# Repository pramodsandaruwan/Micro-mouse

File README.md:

# Micro-mouse
Maze solving micro-mouse robot by Pramod sandaruwan

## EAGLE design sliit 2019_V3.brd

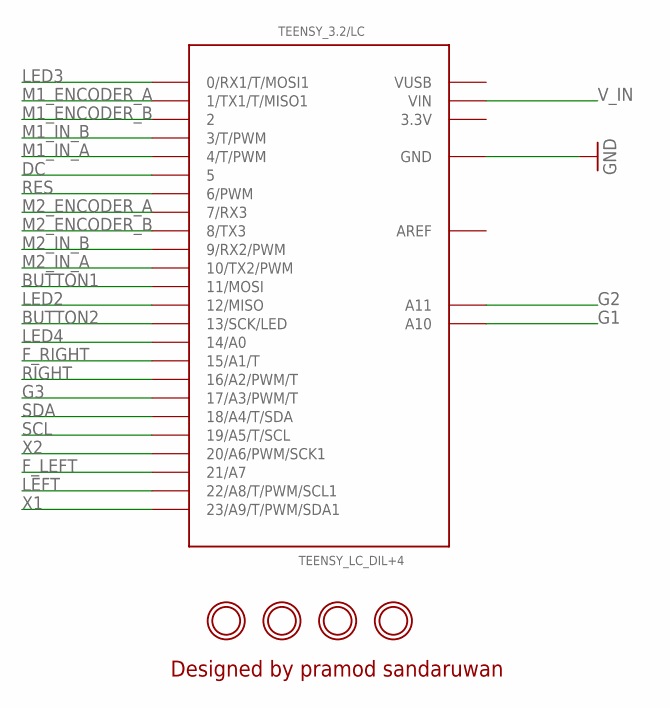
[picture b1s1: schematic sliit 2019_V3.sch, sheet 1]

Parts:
TEENSY_3.2/LC: TEENSY_LC_DIL+4; TEENSY3-DIL+4
U$7, U$10, U$11, U$12: MOUNTINGHOLE2.5; MOUNTINGHOLE_2.5_PLATED

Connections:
3.3V: TEENSY_3.2/LC.3.3V
AREF: TEENSY_3.2/LC.AREF
BUTTON1: TEENSY_3.2/LC.11 (11/MOSI); also elsewhere on the board
BUTTON2: TEENSY_3.2/LC.13 (13/SCK/LED); also elsewhere on the board
DC: TEENSY_3.2/LC.5; also elsewhere on the board
F_LEFT: TEENSY_3.2/LC.21/A7; also elsewhere on the board
F_RIGHT: TEENSY_3.2/LC.15/A1 (15/A1/T); also elsewhere on the board
G1: TEENSY_3.2/LC.A10; also elsewhere on the board
G2: TEENSY_3.2/LC.A11; also elsewhere on the board
G3: TEENSY_3.2/LC.17/A3 (17/A3/PWM/T); also elsewhere on the board
GND: TEENSY_3.2/LC.AGND (GND), TEENSY_3.2/LC.GND; also elsewhere on the board
LED2: TEENSY_3.2/LC.12 (12/MISO); also elsewhere on the board
LED3: TEENSY_3.2/LC.0 (0/RX1/T/MOSI1); also elsewhere on the board
LED4: TEENSY_3.2/LC.14/A0; also elsewhere on the board
LEFT: TEENSY_3.2/LC.22/A8 (22/A8/T/PWM/SCL1); also elsewhere on the board
M1_ENCODER_A: TEENSY_3.2/LC.1 (1/TX1/T/MISO1); also elsewhere on the board
M1_ENCODER_B: TEENSY_3.2/LC.2; also elsewhere on the board
M1_IN_A: TEENSY_3.2/LC.4 (4/T/PWM); also elsewhere on the board
M1_IN_B: TEENSY_3.2/LC.3 (3/T/PWM); also elsewhere on the board
M2_ENCODER_A: TEENSY_3.2/LC.7 (7/RX3); also elsewhere on the board
M2_ENCODER_B: TEENSY_3.2/LC.8 (8/TX3); also elsewhere on the board
M2_IN_A: TEENSY_3.2/LC.10 (10/TX2/PWM); also elsewhere on the board
M2_IN_B: TEENSY_3.2/LC.9 (9/RX2/PWM); also elsewhere on the board
RES: TEENSY_3.2/LC.6 (6/PWM); also elsewhere on the board
RIGHT: TEENSY_3.2/LC.16/A2 (16/A2/PWM/T); also elsewhere on the board
SCL: TEENSY_3.2/LC.19/A5 (19/A5/T/SCL); also elsewhere on the board
SDA: TEENSY_3.2/LC.18/A4 (18/A4/T/SDA); also elsewhere on the board
VUSB: TEENSY_3.2/LC.VUSB
V_IN: TEENSY_3.2/LC.VIN; also elsewhere on the board
X1: TEENSY_3.2/LC.23/A9 (23/A9/T/PWM/SDA1); also elsewhere on the board
X2: TEENSY_3.2/LC.20/A6 (20/A6/PWM/SCK1); also elsewhere on the board

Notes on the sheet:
Designed by pramod sandaruwan

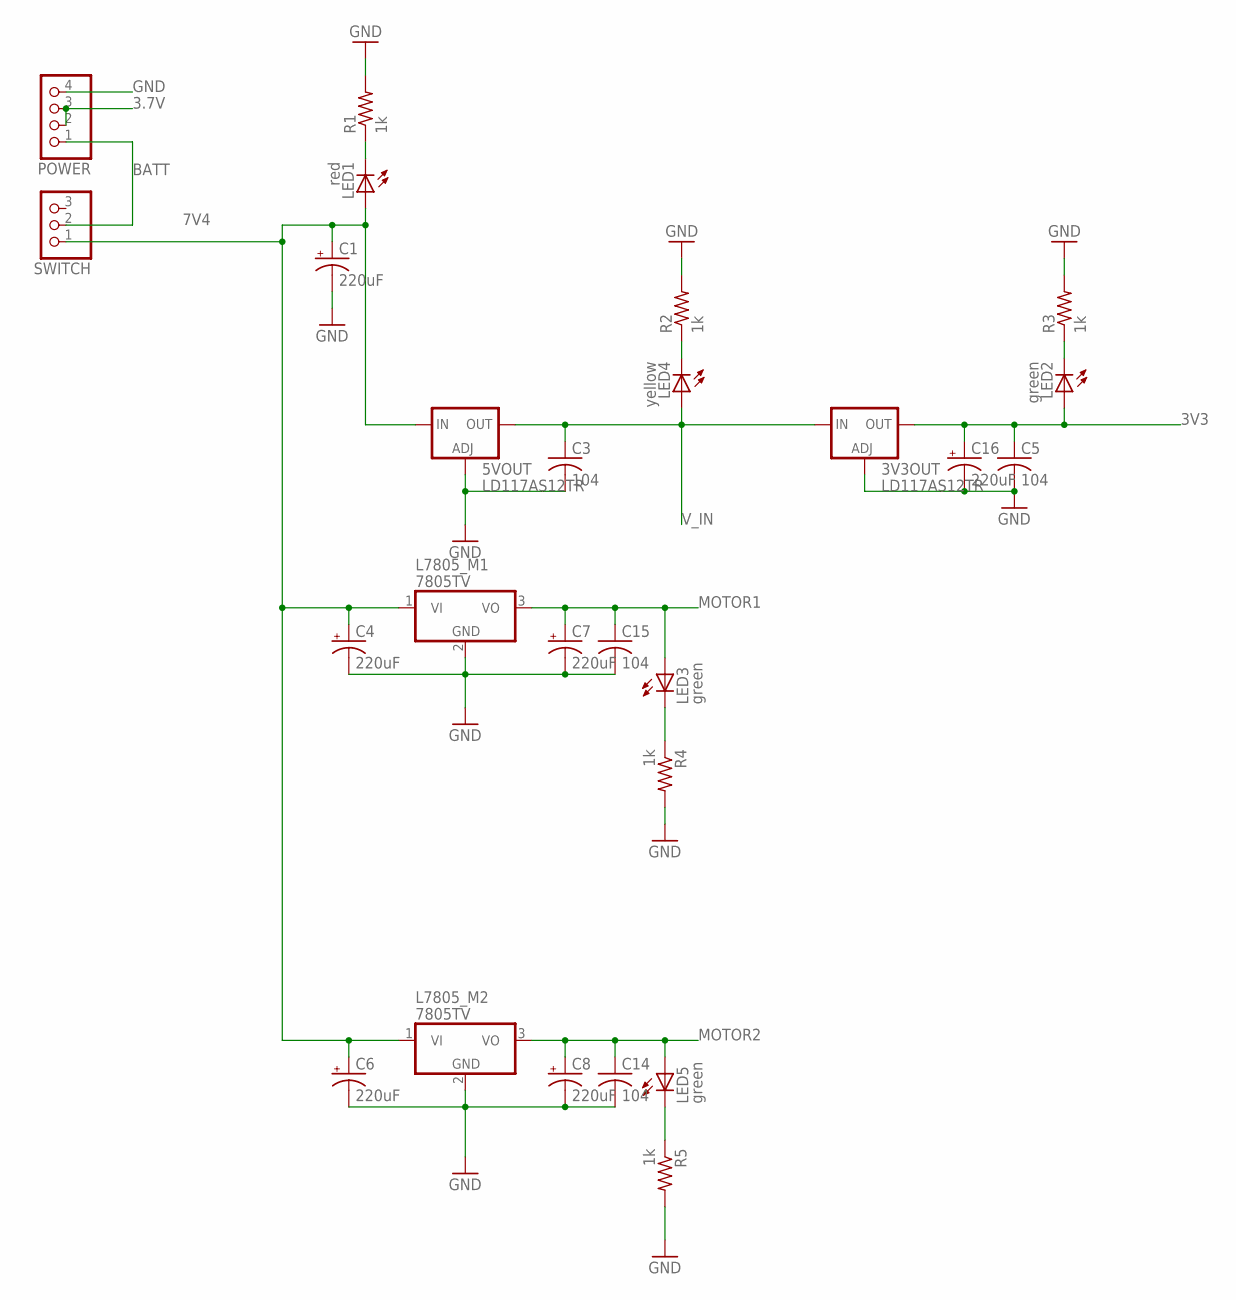
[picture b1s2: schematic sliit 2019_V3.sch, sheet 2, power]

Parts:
3V3OUT, 5VOUT: LD117AS12TR; SOT223
C1, C4, C6, C7, C8, C16: 220uF; 153CLV-0505
C3, C5, C14, C15: 104; C1206
L7805_M1, L7805_M2: 7805TV; TO220V
LED1: red; 1206
LED2, LED3, LED5: green; 1206
LED4: yellow; 1206
POWER: PINHD-1X4; 1X04
R1, R2, R3, R4, R5: 1k; R1206
SWITCH: PINHD-1X3; 1X03

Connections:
3.7V: POWER.2, POWER.3
3V3: 3V3OUT.4 (OUT), C5.1, C16.+, LED2.A; also elsewhere on the board
7V4: 5VOUT.3 (IN), C1.+, C4.+, C6.+, L7805_M1.1 (VI), L7805_M2.1 (VI), LED1.A, SWITCH.1
BATT: POWER.1, SWITCH.2
GND: 3V3OUT.1 (ADJ), 5VOUT.1 (ADJ), C1.-, C3.2, C4.-, C5.2, C6.-, C7.-, C8.-, C14.2, C15.2, C16.-, L7805_M1.2 (GND), L7805_M2.2 (GND), POWER.4, R1.2, R2.2, R3.2, R4.2, R5.2; also elsewhere on the board
MOTOR1: C7.+, C15.1, L7805_M1.3 (VO), LED3.A; also elsewhere on the board
MOTOR2: C8.+, C14.1, L7805_M2.3 (VO), LED5.A; also elsewhere on the board
unnamed: LED3.C, R4.1
unnamed: LED1.C, R1.1
unnamed: LED5.C, R5.1
unnamed: LED4.C, R2.1
unnamed: LED2.C, R3.1
V_IN: 3V3OUT.3 (IN), 5VOUT.4 (OUT), C3.1, LED4.A; also elsewhere on the board

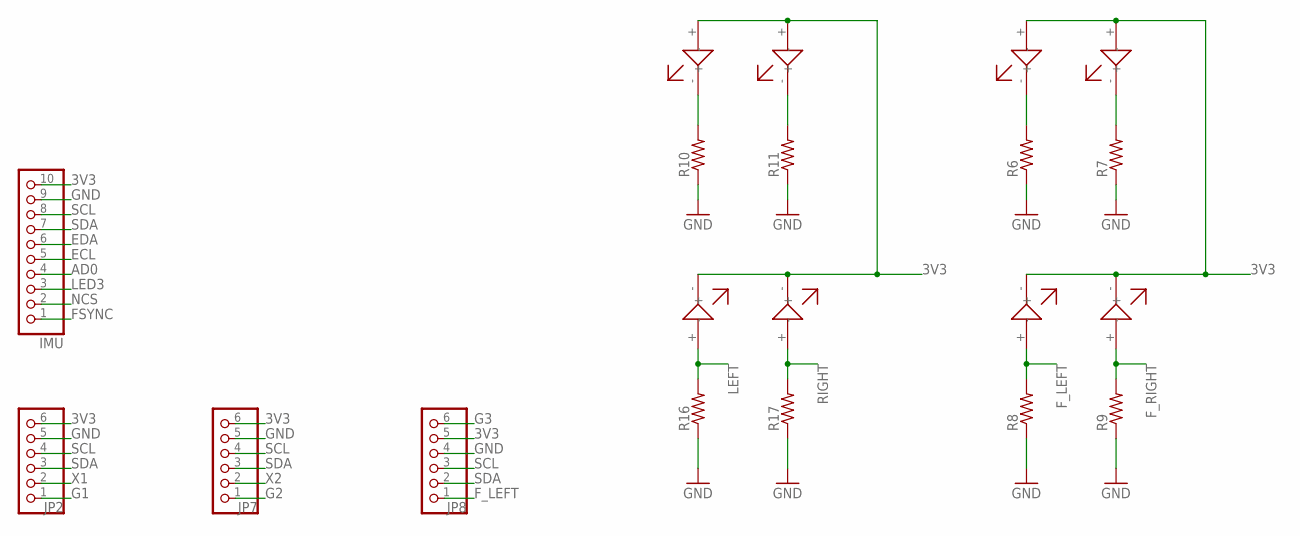
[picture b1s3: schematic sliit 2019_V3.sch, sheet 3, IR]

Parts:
IMU: PINHD-1X10; 1X10
JP2, JP7, JP8: PINHD-1X6; 1X06
R6, R7, R8, R9, R10, R11, R16, R17: R-US_R0805; R0805
U$1, U$4, U$5, U$6, U$8, U$9, U$14, U$15: IR

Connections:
3V3: IMU.10, JP2.6, JP7.6, JP8.5, U$1.+, U$4.+, U$5.-, U$6.-, U$8.+, U$9.+, U$14.-, U$15.-; also elsewhere on the board
AD0: IMU.4
ECL: IMU.5
EDA: IMU.6
FSYNC: IMU.1
F_LEFT: JP8.1, R8.2, U$5.+; also elsewhere on the board
F_RIGHT: R9.2, U$6.+; also elsewhere on the board
G1: JP2.1; also elsewhere on the board
G2: JP7.1; also elsewhere on the board
G3: JP8.6; also elsewhere on the board
GND: IMU.9, JP2.5, JP7.5, JP8.4, R6.1, R7.1, R8.1, R9.1, R10.1, R11.1, R16.1, R17.1; also elsewhere on the board
LED3: IMU.3; also elsewhere on the board
LEFT: R16.2, U$14.+; also elsewhere on the board
unnamed: R7.2, U$4.-
unnamed: R6.2, U$1.-
unnamed: R11.2, U$9.-
unnamed: R10.2, U$8.-
NCS: IMU.2
RIGHT: R17.2, U$15.+; also elsewhere on the board
SCL: IMU.8, JP2.4, JP7.4, JP8.3; also elsewhere on the board
SDA: IMU.7, JP2.3, JP7.3, JP8.2; also elsewhere on the board
X1: JP2.2; also elsewhere on the board
X2: JP7.2; also elsewhere on the board

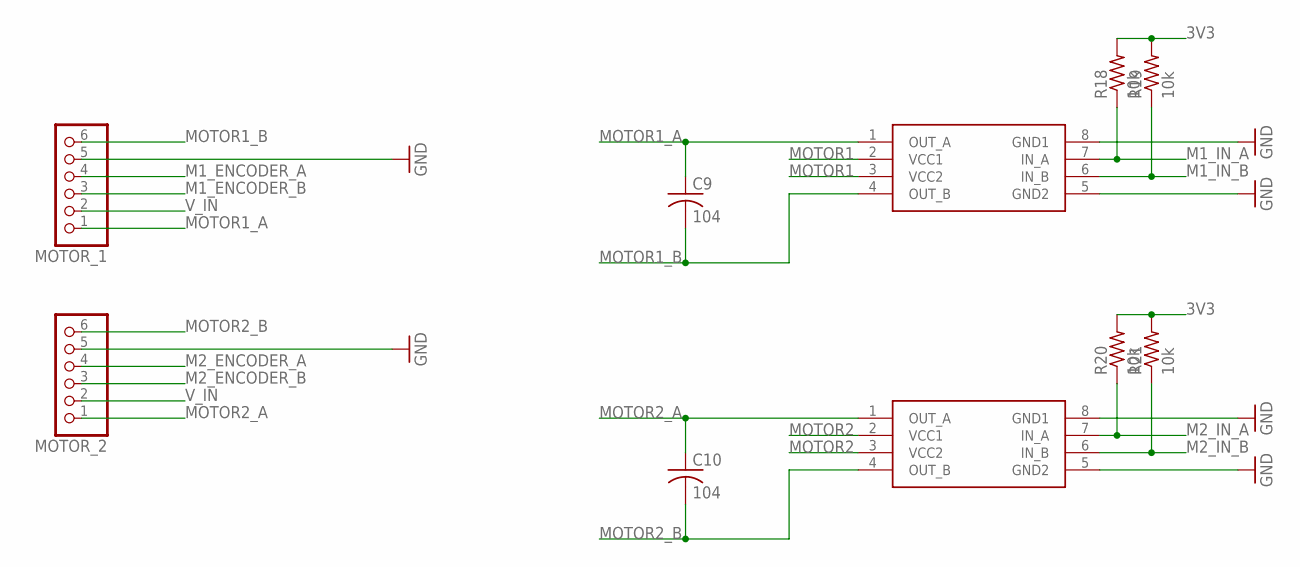
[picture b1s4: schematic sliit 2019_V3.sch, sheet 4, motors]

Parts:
C9, C10: 104; C1206
MOTOR_1, MOTOR_2: PINHD-1X6; 1X06
R18, R19, R20, R21: 10k; R1206
U$2, U$3: L9110

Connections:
3V3: R18.2, R19.2, R20.2, R21.2; also elsewhere on the board
GND: MOTOR_1.5, MOTOR_2.5, U$2.5 (GND2), U$2.8 (GND1), U$3.5 (GND2), U$3.8 (GND1); also elsewhere on the board
M1_ENCODER_A: MOTOR_1.4; also elsewhere on the board
M1_ENCODER_B: MOTOR_1.3; also elsewhere on the board
M1_IN_A: R18.1, U$2.7 (IN_A); also elsewhere on the board
M1_IN_B: R19.1, U$2.6 (IN_B); also elsewhere on the board
M2_ENCODER_A: MOTOR_2.4; also elsewhere on the board
M2_ENCODER_B: MOTOR_2.3; also elsewhere on the board
M2_IN_A: R20.1, U$3.7 (IN_A); also elsewhere on the board
M2_IN_B: R21.1, U$3.6 (IN_B); also elsewhere on the board
MOTOR1: U$2.2 (VCC1), U$2.3 (VCC2); also elsewhere on the board
MOTOR1_A: C9.1, MOTOR_1.1, U$2.1 (OUT_A)
MOTOR1_B: C9.2, MOTOR_1.6, U$2.4 (OUT_B)
MOTOR2: U$3.2 (VCC1), U$3.3 (VCC2); also elsewhere on the board
MOTOR2_A: C10.1, MOTOR_2.1, U$3.1 (OUT_A)
MOTOR2_B: C10.2, MOTOR_2.6, U$3.4 (OUT_B)
V_IN: MOTOR_1.2, MOTOR_2.2; also elsewhere on the board

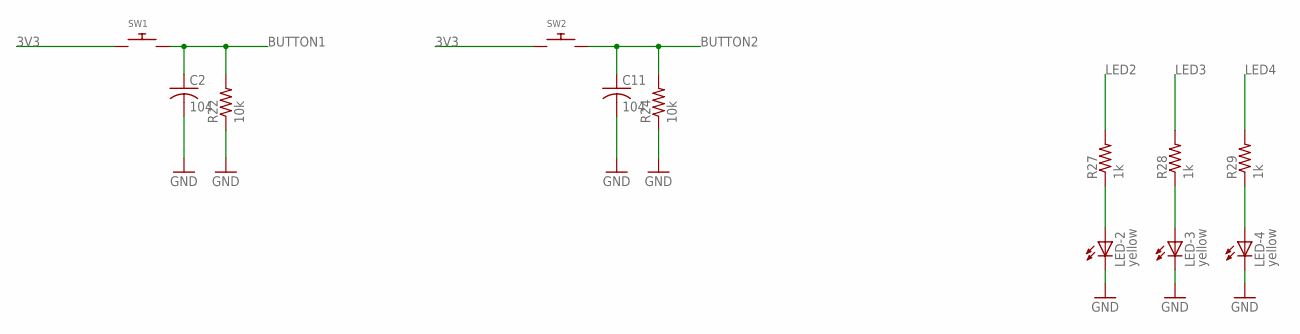
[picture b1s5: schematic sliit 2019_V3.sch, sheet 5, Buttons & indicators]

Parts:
C2, C11: 104; C1206
LED-2, LED-3, LED-4: yellow; 1206
R22, R24: 10k; R1206
R27, R28, R29: 1k; R1206
SW1, SW2: SWITCH_PUSHBUTTONC&K_KSS; BTN_CK_KSS

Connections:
3V3: SW1.P$1, SW2.P$1; also elsewhere on the board
BUTTON1: C2.1, R22.2, SW1.P$2; also elsewhere on the board
BUTTON2: C11.1, R24.2, SW2.P$2; also elsewhere on the board
GND: C2.2, C11.2, LED-2.C, LED-3.C, LED-4.C, R22.1, R24.1; also elsewhere on the board
LED2: R27.2; also elsewhere on the board
LED3: R28.2; also elsewhere on the board
LED4: R29.2; also elsewhere on the board
unnamed: LED-2.A, R27.1
unnamed: LED-3.A, R28.1
unnamed: LED-4.A, R29.1

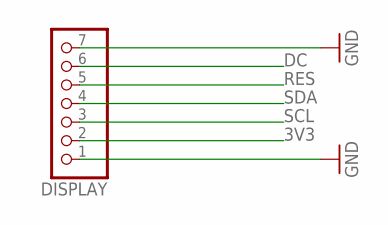
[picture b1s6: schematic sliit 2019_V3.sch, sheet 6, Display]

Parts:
DISPLAY: PINHD-1X7; 1X07

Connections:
3V3: DISPLAY.2; also elsewhere on the board
DC: DISPLAY.6; also elsewhere on the board
GND: DISPLAY.1, DISPLAY.7; also elsewhere on the board
RES: DISPLAY.5; also elsewhere on the board
SCL: DISPLAY.3; also elsewhere on the board
SDA: DISPLAY.4; also elsewhere on the board

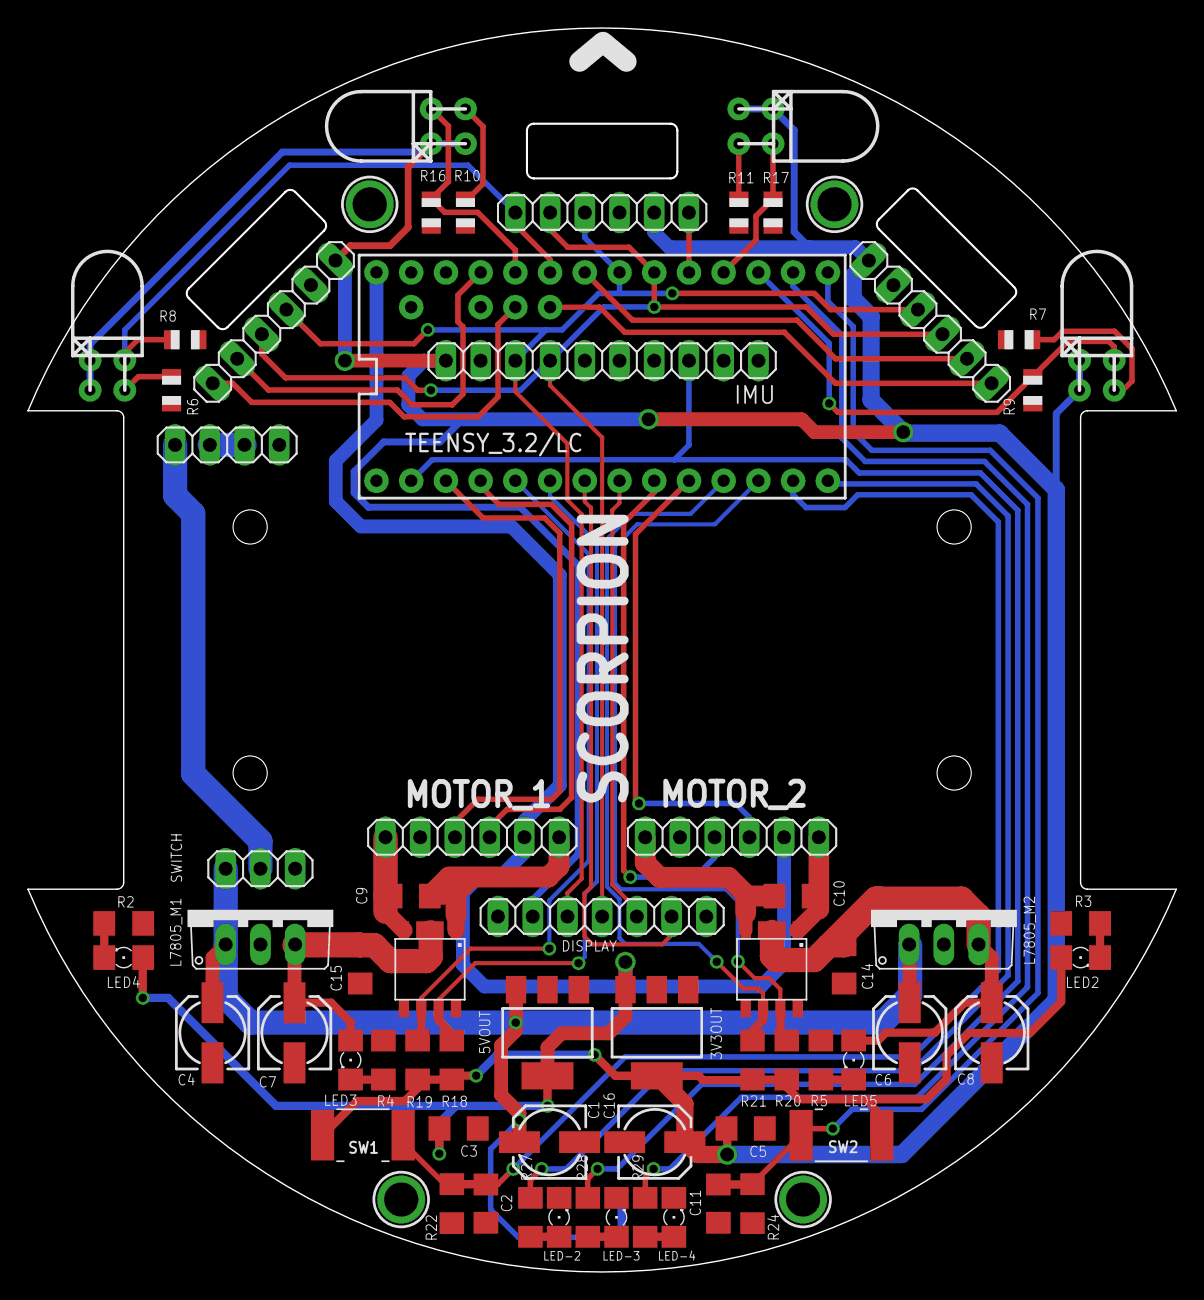
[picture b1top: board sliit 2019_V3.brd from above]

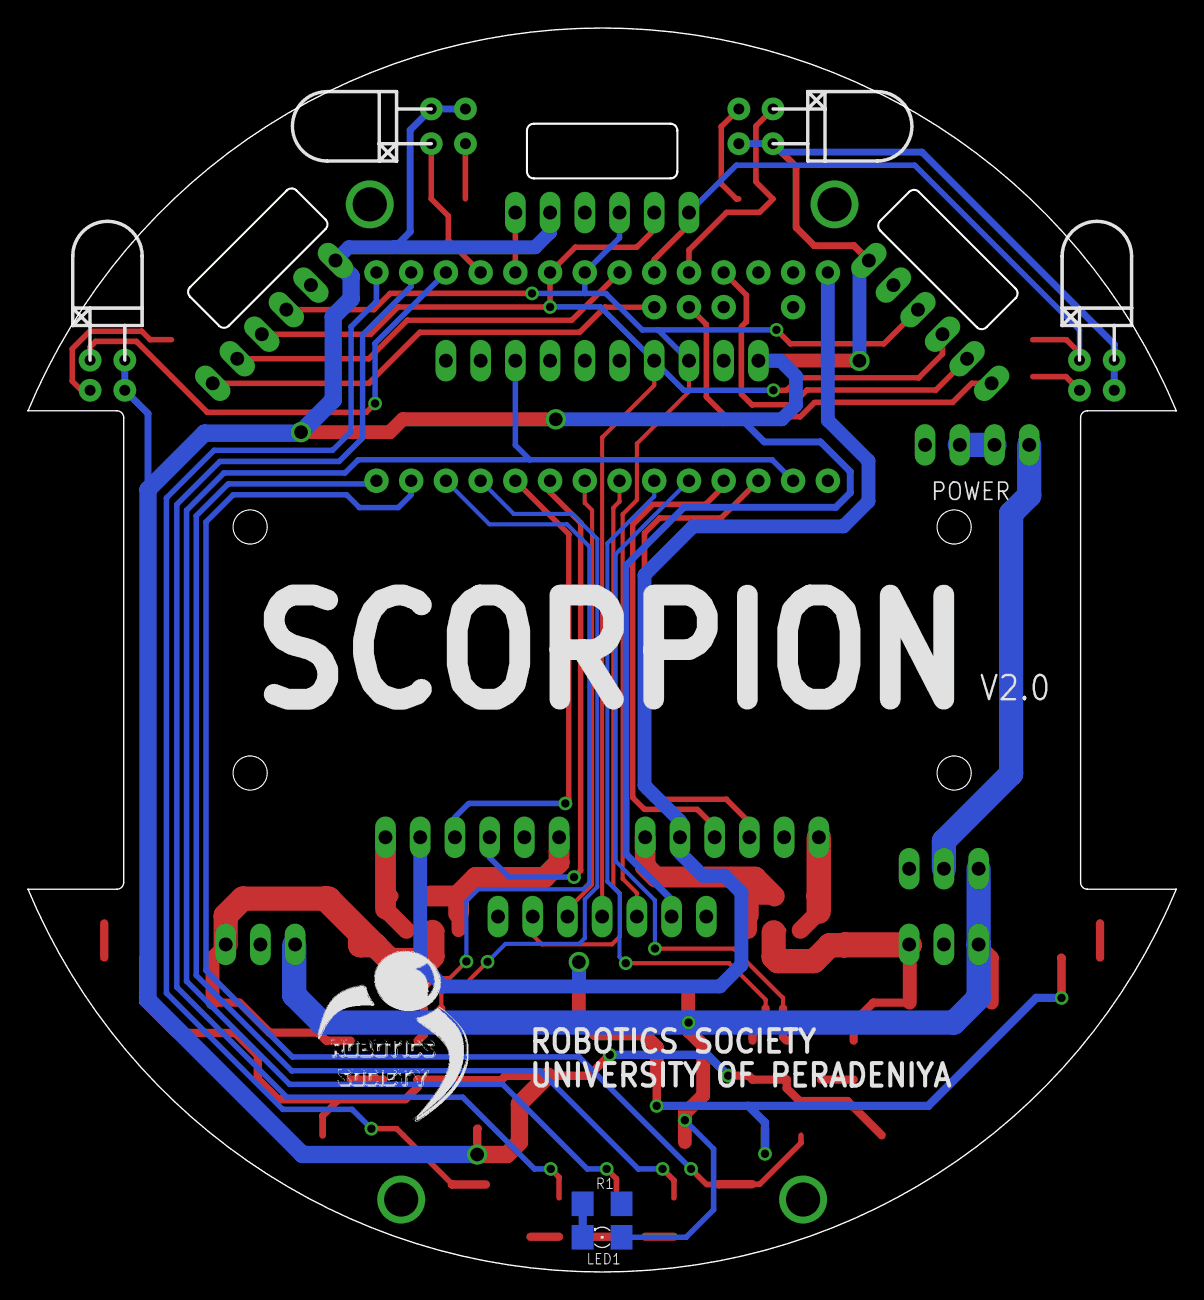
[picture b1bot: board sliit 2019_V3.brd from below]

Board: 2 copper layers, 84.0 x 91.0 mm, 74 parts (6 on the bottom side), 50 nets.
